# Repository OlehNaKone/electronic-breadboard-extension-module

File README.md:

# electronic-breadboard-extension-module

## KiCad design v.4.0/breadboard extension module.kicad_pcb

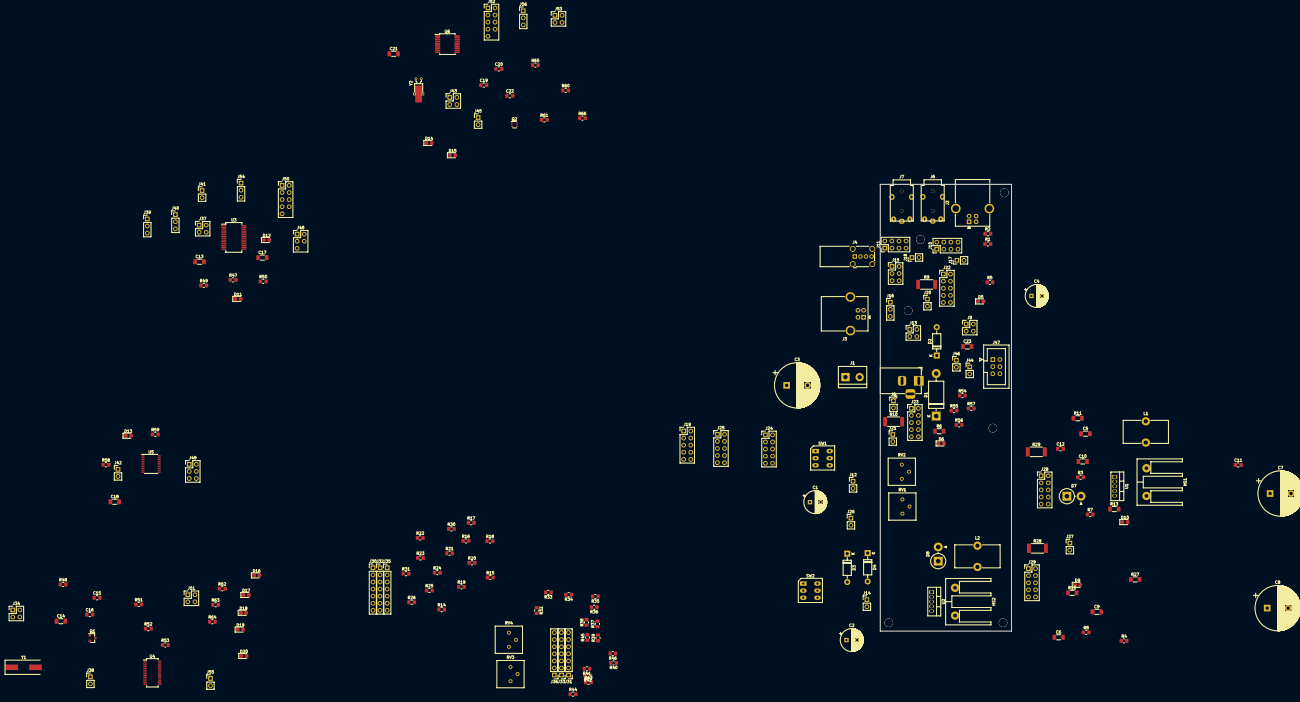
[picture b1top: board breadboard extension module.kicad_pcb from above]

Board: 2 copper layers, 47.0 x 160.0 mm, 185 parts (0 on the bottom side), 169 nets, no tracks yet.

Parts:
C1, C2: 100uF35V; CP_Radial_D8.0mm_P3.80mm
C3, C7, C8: 1000uF50V; CP_Radial_D16.0mm_P7.50mm
C4: 100uF16V; CP_Radial_D8.0mm_P3.80mm
C5, C6, C9, C10, C13: 100nF; C_1206_3216Metric_Pad1.33x1.80mm_HandSolder
C11, C12: 100nF; C_0805_2012Metric_Pad1.18x1.45mm_HandSolder
C14, C17, C18, C21, C23: 1uF; C_1206_3216Metric_Pad1.33x1.80mm_HandSolder
C15, C16: 1uF; C_0805_2012Metric_Pad1.18x1.45mm_HandSolder
C19, C20: 18pF; C_0805_2012Metric_Pad1.18x1.45mm_HandSolder
C22: 10nF; C_0805_2012Metric_Pad1.18x1.45mm_HandSolder
D1: 1N5408; D_DO-201AD_P15.24mm_Horizontal
D2, D3, D4: 1N5819; D_DO-41_SOD81_P10.16mm_Horizontal
D5: usbpower.red; LED_0805_2012Metric_Castellated
D6: mainpower.green; LED_0805_2012Metric_Castellated
D7, D8: 1N5822; D_DO-201AD_P5.08mm_Vertical_AnodeUp
D9: vinvreg.red; LED_0805_2012Metric_Castellated
D10: stdnreg.green; LED_0805_2012Metric_Castellated
D11: ft232.txd; LED_0805_2012Metric_Castellated
D12: ft232.rxd; LED_0805_2012Metric_Castellated
D13: avrisp.prog; LED_0805_2012Metric_Castellated
D14: ch340.txd; LED_0805_2012Metric_Castellated
D15: ch340.rxd; LED_0805_2012Metric_Castellated
D16: fe11s.port1; LED_0805_2012Metric_Castellated
D17: fe11s.port3; LED_0805_2012Metric_Castellated
D18: fe11s.port2; LED_0805_2012Metric_Castellated
D19: fe11s.port4; LED_0805_2012Metric_Castellated
D20: fe11s.active; LED_0805_2012Metric_Castellated
HS1: vinvreg.heatsink; Heatsink_16.36x16mm_2xFixation1.35mm
HS2: stdnreg.heatsink; Heatsink_16.36x16mm_2xFixation1.35mm
J1: Screw_Terminal_01x02; TerminalBlock_bornier-2_P5.08mm
J2: USB-B-1; USB_B_OST_USB-B1HSxx_Horizontal
J3: USB-B-2; USB_B_OST_USB-B1HSxx_Horizontal
J4: USB-A-1; USB_A_Wuerth_614004134726_Horizontal
J5: Barrel_Jack_Switch; BarrelJack_Horizontal
J6: AudioJack1; Jack_3.5mm_ST-17D-070_Horizontal
J7: AudioJack2; Jack_3.5mm_ST-17D-070_Horizontal
J8: mainpower.jackswitch; PinHeader_1x02_P2.54mm_Vertical
J9: usbpower.muxsw; PinHeader_2x02_P2.54mm_Vertical
J10: AudioJack1.conn; PinHeader_2x04_P2.54mm_Vertical
J11: AudioJack2.conn; PinHeader_2x04_P2.54mm_Vertical
J12: stdnreg.disable; PinHeader_1x02_P2.54mm_Vertical
J13: addusb.datasw; PinHeader_2x02_P2.54mm_Vertical
J14: vinvreg.disable; PinHeader_1x02_P2.54mm_Vertical
J15: addusb.vccsw; PinHeader_2x03_P2.54mm_Vertical
J16: usbb1.vccsw; PinHeader_1x03_P2.54mm_Vertical
J17: AudioJack1.gnd; PinHeader_1x02_P2.54mm_Vertical
J18: AudioJack2.gnd; PinHeader_1x02_P2.54mm_Vertical
J19, J24, J25: mainpower.gnd; PinHeader_2x05_P2.54mm_Vertical
J20: usbpower.current; PinHeader_1x02_P2.54mm_Vertical
J21: mainpower.current; PinHeader_1x02_P2.54mm_Vertical
J22: usbpower.vcc; PinHeader_2x05_P2.54mm_Vertical
J23: mainpower.vcc; PinHeader_2x05_P2.54mm_Vertical
J26: stdnreg.outcurrent; PinHeader_1x02_P2.54mm_Vertical
J27: vinvreg.outcurrent; PinHeader_1x02_P2.54mm_Vertical
J28: stdnreg.vout; PinHeader_2x05_P2.54mm_Vertical
J29: vinvreg.vout; PinHeader_2x05_P2.54mm_Vertical
J30, J32, J35: stdnreg.vsw; PinHeader_1x07_P2.54mm_Vertical
J31, J33, J36: vinveg.vsw; PinHeader_1x07_P2.54mm_Vertical
J34: fe11s.usbsw; PinHeader_2x02_P2.54mm_Vertical
J37: ft232.usbsw; PinHeader_2x02_P2.54mm_Vertical
J38: fe11s.vccsw; PinHeader_1x02_P2.54mm_Vertical
J39: ft232.ressw; PinHeader_1x03_P2.54mm_Vertical
J40: ft232.vcciosw; PinHeader_1x03_P2.54mm_Vertical
J41: ft232.vccsw; PinHeader_1x02_P2.54mm_Vertical
J42: buff.vccsw; PinHeader_1x02_P2.54mm_Vertical
J43: ch340.usbsw; PinHeader_2x02_P2.54mm_Vertical
J44: avrisp.ressw; PinHeader_1x02_P2.54mm_Vertical
J45: ch340.vccsw; PinHeader_1x02_P2.54mm_Vertical
J46: avrisp.vccsw; PinHeader_1x02_P2.54mm_Vertical
J47: AVR-ISP-6; IDC-Header_2x03_P2.54mm_Vertical
J48: ft232.addport; PinHeader_2Rows-05Pins_P2.54mm_Vertical
J49: buff.addport; PinHeader_2x03_P2.54mm_Vertical
J50: ft232.rs232port; PinHeader_2Rows-09Pins_P2.54mm_Vertical
J51: fe11s.addport; PinHeader_2x02_P2.54mm_Vertical
J52: ch340.rs232port; PinHeader_2Rows-09Pins_P2.54mm_Vertical
J53: ch340.addport; PinHeader_2x02_P2.54mm_Vertical
J54: ft232.uartport; PinHeader_1x03_P2.54mm_Vertical
J55: fe11s.connected; PinHeader_1x02_P2.54mm_Vertical
J56: ch340.uartport; PinHeader_1x03_P2.54mm_Vertical
L1: 300uH; L_Toroid_Vertical_L16.0mm_W8.0mm_P7.62mm
L2: 150 (68-220) uH; L_Toroid_Vertical_L16.0mm_W8.0mm_P7.62mm
Q1: BC847; SOT-23
Q2: BC857BDW1; SOT-363_SC-70-6
R1, R2: 10; R_0805_2012Metric_Pad1.20x1.40mm_HandSolder
R3, R4, R7, R8: 47k; R_0805_2012Metric_Pad1.20x1.40mm_HandSolder
R5, R51, R62, R63, R64: 2k; R_0805_2012Metric_Pad1.20x1.40mm_HandSolder
R6, R12, R13: 2.4k; R_1206_3216Metric_Pad1.30x1.75mm_HandSolder
R9, R10, R28, R29: 0.1R; R_2512_6332Metric_Pad1.40x3.35mm_HandSolder
R11, R27: 1.6k; R_1206_3216Metric_Pad1.30x1.75mm_HandSolder
R14, R32: 6.2k; R_0805_2012Metric_Pad1.20x1.40mm_HandSolder
R15, R33: 240 1%; R_0805_2012Metric_Pad1.20x1.40mm_HandSolder
R16, R34: 5.1k; R_0805_2012Metric_Pad1.20x1.40mm_HandSolder
R17, R25, R35, R43, R54, R55, R56, R57: 100; R_0805_2012Metric_Pad1.20x1.40mm_HandSolder
R18, R36: 3.3k 1%; R_0805_2012Metric_Pad1.20x1.40mm_HandSolder
R19, R37: 470 1%; R_0805_2012Metric_Pad1.20x1.40mm_HandSolder
R20, R38: 4.02k 1%; R_0805_2012Metric_Pad1.20x1.40mm_HandSolder
R21, R22, R39, R40: 20k 1%; R_0805_2012Metric_Pad1.20x1.40mm_HandSolder
R23, R41: 2.37k; R_0805_2012Metric_Pad1.20x1.40mm_HandSolder
R24, R42: 1.87k; R_0805_2012Metric_Pad1.20x1.40mm_HandSolder
R26, R44: 754.472; R_0805_2012Metric_Pad1.20x1.40mm_HandSolder
R30, R45: 2.37k 1%; R_0805_2012Metric_Pad1.20x1.40mm_HandSolder
R31, R46: 3.74k 1%; R_0805_2012Metric_Pad1.20x1.40mm_HandSolder
R47, R52, R53, R58, R61, R66: 10k; R_0805_2012Metric_Pad1.20x1.40mm_HandSolder
R48: 2k7 1%; R_0805_2012Metric_Pad1.20x1.40mm_HandSolder
R49, R50, R59, R60, R65: 1k; R_0805_2012Metric_Pad1.20x1.40mm_HandSolder
RV1, RV3: 45k; Potentiometer_Bourns_3386P_Vertical
RV2, RV4: 5k; Potentiometer_Bourns_3386P_Vertical
SW1, SW2: SW_Push_DPDT; SW_Push_DPDT_8.4x8.4mm
U1, U2: LM2596T-ADJ; TO-220-5_Vertical
U3: FT232RL; SSOP-28_5.3x10.2mm_P0.65mm
U4: FE1.1S; SSOP-28_3.9x9.9mm_P0.635mm
U5: 74HC244; SSOP-20_4.4x6.5mm_P0.65mm
U6: CH340T; SSOP-20_5.3x7.2mm_P0.65mm
Y1: 12MHz; Crystal_SMD_HC49-SD
Y2: 12MHz; Crystal_DS26_D2.0mm_L6.0mm_Horizontal_1EP_style2

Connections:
/AudioJack1.R1: J6.R1, J10.5, J10.6
/AudioJack1.R2: J6.R2, J10.3, J10.4
/AudioJack1.S: J6.S, J10.1, J10.2
/AudioJack1.T: J6.T, J10.7, J10.8
/AudioJack2.R1: J7.R1, J11.5, J11.6
/AudioJack2.R2: J7.R2, J11.3, J11.4
/AudioJack2.S: J7.S, J11.1, J11.2
/AudioJack2.T: J7.T, J11.7, J11.8
/avrisp.miso: R54.1, U5.2
/avrisp.mosi: R55.1, U5.16
/avrisp.progled: D13.1, U5.9
/avrisp.sck: R56.1, U5.14
/avrisp.~reset~: R57.1, U5.12
/buff.i0: J49.1, U5.17
/buff.i1: J49.3, U5.15
/buff.i2: J49.5, U5.13
/buff.o0: J49.2, U5.3
/buff.o1: J49.4, U5.5
/buff.o2: J49.6, U5.7
/ch340.ckoh: J53.1, U6.1
/ch340.ckol: J53.3, U6.2
/ch340.d+: J43.1, U4.11
/ch340.d-: J43.3, U4.10
/ch340.r232: J53.4, U6.18
/ch340.rxd: J52.2, J56.2, R66.2, U6.4
/ch340.txd: J52.3, J56.1, R61.2, U6.3
/ch340.~cts~: J52.8, U6.11
/ch340.~dcd~: J52.1, U6.14
/ch340.~dsr~: J52.6, U6.12
/ch340.~dtr~: J52.4, U6.15
/ch340.~nos~: J53.2, U6.20
/ch340.~ri~: J52.9, U6.13
/ch340.~rts~: J52.7, U6.16
/fe11s.connected: J39.1, J55.1, J55.2, Q1.3, R51.1
/fe11s.d+: J34.2, U4.16
/fe11s.d-: J34.4, U4.15
/fe11s.led13: R62.1, U4.23
/fe11s.led24: R63.1, U4.24
/fe11s.leddrv: D16.2, D17.1, D18.2, D19.1, D20.2, U4.22
/fe11s.p3d+: J51.1, U4.7
/fe11s.p3d-: J51.3, U4.6
/fe11s.p4d+: J51.2, U4.4
/fe11s.p4d-: J51.4, U4.5
/fe11s.vbus: C14.1, J38.2, R51.2, R52.1, R53.1, U4.18, U4.20
/fe11s.~connected~: Q1.1, R53.2, U4.25
/ft232.cbus0: D11.1, J48.1, U3.23
/ft232.cbus1: D12.1, J48.2, U3.22
/ft232.cbus2: J48.3, U3.13
/ft232.cbus3: J48.4, U3.14
/ft232.cbus4: J48.5, U3.12
/ft232.d+: J37.1, U4.9
/ft232.d-: J37.3, U4.8
/ft232.rxd: J50.2, J54.2, U3.5
/ft232.txd: J50.3, J54.1, U3.1
/ft232.~cts~: J50.8, R58.2, U3.11, U5.1, U5.11
/ft232.~dcd~: J50.1, U3.10, U5.4
/ft232.~dsr~: J50.6, U3.9, U5.8
/ft232.~dtr~: J50.4, U3.2, U5.18
/ft232.~ri~: J50.9, U3.6
/ft232.~rts~: J50.7, U3.3, U5.6
/mainpower.vcc: C3.1, D1.1, D2.1, J21.1, R6.2, R10.1, SW1.3, SW1.6, SW2.3, SW2.6
/stdnreg.1.81V: J30.1, R25.1, R26.2
/stdnreg.3.33V: J30.2, R23.1, R24.2
/stdnreg.5.15V: J30.3, R22.1, R23.2, R31.1
/stdnreg.7.5V: J30.4, R21.1, R22.2, R30.1, R31.2
/stdnreg.9.2V: J30.5, R20.1, R21.2, R30.2
/stdnreg.12.3V: J30.6, R19.1, R20.2
/stdnreg.15.2V: J30.7, R17.1, R18.2
/stdnreg.19.2V: J35.7, R15.1, R16.2
/stdnreg.24.15V: J35.6, R14.2
/stdnreg.coarse1: J35.2, RV1.1
/stdnreg.coarse2: J35.3, RV1.2, RV1.3
/stdnreg.fb: C12.1, J32.1, J32.2, J32.3, J32.4, J32.5, J32.6, J32.7, R11.1, U1.4
/stdnreg.fine1: J35.4, RV2.1
/stdnreg.fine2: J35.5, RV2.2, RV2.3
/stdnreg.vout: C12.2, J26.2, J28.1, J28.2, J28.3, J28.4, J28.5, J28.6, J28.7, J28.8, J28.9, J28.10, J35.1, R26.1, R29.2
/usba1.d+: J4.3, J13.2
/usba1.d-: J4.2, J13.4
/usba1.vbus: J4.1, J15.4, J15.6
/usbb1.d+: J34.1, R1.2
/usbb1.d-: J34.3, R2.2
/usbb1.vbus: J2.1, J16.1, J16.2
/usbb2.d+: J3.3, J13.1
/usbb2.d-: J3.2, J13.3
/usbb2.vbus: J3.1, J15.3, J15.5
/usbpower.vcc: C4.1, J9.1, J9.3, J15.1, J15.2, J16.3, J20.1, J38.1, J41.1, J42.1, J45.1, J46.1, R5.2, R9.1
/vinvreg.1.81V: J31.1, R43.1, R44.2
/vinvreg.3.33V: J31.2, R41.1, R42.2
/vinvreg.5.15V: J31.3, R40.1, R41.2, R46.1
/vinvreg.7.5V: J31.4, R39.1, R40.2, R45.1, R46.2
/vinvreg.9.2V: J31.5, R38.1, R39.2, R45.2
/vinvreg.12.3V: J31.6, R37.1, R38.2
/vinvreg.15.2V: J31.7, R35.1, R36.2
/vinvreg.19.2V: J36.7, R33.1, R34.2
/vinvreg.24.15V: J36.6, R32.2
/vinvreg.coarse1: J36.2, RV3.1
/vinvreg.coarse2: J36.3, RV3.2, RV3.3
/vinvreg.fb: C11.1, J33.1, J33.2, J33.3, J33.4, J33.5, J33.6, J33.7, R27.2, U2.4
/vinvreg.fine1: J36.4, RV4.1
/vinvreg.fine2: J36.5, RV4.2, RV4.3
/vinvreg.vout: J27.2, J29.1, J29.2, J29.3, J29.4, J29.5, J29.6, J29.7, J29.8, J29.9, J29.10, R27.1, R28.2
GNDD: C1.2, C2.2, C3.2, C4.2, C7.2, C8.1, C9.1, C10.2, C11.2, C13.1, C14.2, C15.1, C16.1, C17.2, C18.2, C19.1, C20.1, C21.1, C22.1, C23.2, D4.2, D5.1, D6.1, D7.2, D10.1, D14.1, D15.1, J1.2, J2.4, J2.5, J3.4, J3.5, J4.4, J4.5, J5.2, J17.1, J17.2, J18.1, J18.2, J19.1, J19.2, J19.3, J19.4, J19.5, J19.6, J19.7, J19.8, J19.9, J19.10, J24.1, J24.2, J24.3, J24.4, J24.5, J24.6, J24.7, J24.8, J24.9, J24.10, J25.1, J25.2, J25.3, J25.4, J25.5, J25.6, J25.7, J25.8, J25.9, J25.10, J36.1, J47.6, J50.5, J52.5, J54.3, J56.3, L2.2, Q1.2, R7.2, R11.2, R12.1, R44.1, R47.1, R48.1, R64.1, U1.3, U3.7, U3.18, U3.21, U3.25, U3.26, U4.1, U4.19, U5.10, U5.19, U6.8
unnamed: C1.1, C5.1, J12.1, SW1.2, SW1.5, U1.1
unnamed: C2.1, D3.2, SW2.2, SW2.5
unnamed: C5.2, J12.2, R3.2
unnamed: C6.1, D3.1, D4.1, U2.1
unnamed: C6.2, R4.2
unnamed: C8.2, C9.2, D8.2, D9.1, J14.2, J27.1, R8.2, R28.1, U2.3
unnamed: C7.1, C10.1, J26.1, L1.2, R13.2, R29.1
unnamed: C13.2, J40.1, U3.17
unnamed: C15.2, U4.13, U4.21
unnamed: C16.2, U4.28
unnamed: C17.1, J39.3, J40.3, J41.2, R49.1, R50.1, U3.20
unnamed: C18.1, J42.2, R58.1, R59.1, U5.20
unnamed: C19.2, U6.9, Y2.1
unnamed: C20.2, U6.10, Y2.2
unnamed: C21.2, J45.2, R60.1, R65.1, U6.19
unnamed: C22.2, U6.5
unnamed: C23.1, J46.2, J47.2
unnamed: D1.2, J1.1, J5.1
unnamed: D2.2, J9.2, J9.4
unnamed: D5.2, R5.1
unnamed: D6.2, R6.1
unnamed: D7.1, L1.1, U1.2
unnamed: D8.1, L2.1, U2.2
unnamed: D9.2, R12.2
unnamed: D10.2, R13.1
unnamed: D11.2, R49.2
unnamed: D12.2, R50.2
unnamed: D13.2, R59.2
unnamed: D14.2, Q2.3
unnamed: D15.2, Q2.6
unnamed: D16.1, D17.2, R62.2
unnamed: D18.1, D19.2, R63.2
unnamed: D20.1, R64.2
unnamed: J2.2, R2.1
unnamed: J2.3, R1.1
unnamed: J5.3, J8.1, J8.2
unnamed: J14.1, R4.1, R8.1, U2.5
unnamed: J20.2, J22.1, J22.2, J22.3, J22.4, J22.5, J22.6, J22.7, J22.8, J22.9, J22.10, R9.2
unnamed: J21.2, J23.1, J23.2, J23.3, J23.4, J23.5, J23.6, J23.7, J23.8, J23.9, J23.10, R10.2
unnamed: J37.2, U3.15
unnamed: J37.4, U3.16
unnamed: J39.2, R47.2, U3.19
unnamed: J40.2, U3.4
unnamed: J43.2, U6.6
unnamed: J43.4, U6.7
unnamed: J44.1, R57.2
unnamed: J44.2, J47.5
unnamed: J47.1, R54.2
unnamed: J47.3, R56.2
unnamed: J47.4, R55.2
unnamed: Q2.1, R65.2
unnamed: Q2.2, R66.1
unnamed: Q2.4, R60.2
unnamed: Q2.5, R61.1
unnamed: R3.1, R7.1, U1.5
unnamed: R14.1, R15.2
unnamed: R16.1, R17.2
unnamed: R18.1, R19.2
unnamed: R24.1, R25.2
unnamed: R32.1, R33.2
unnamed: R34.1, R35.2
unnamed: R36.1, R37.2
unnamed: R42.1, R43.2
unnamed: R48.2, U4.14
unnamed: R52.2, U4.26
unnamed: U4.2, Y1.1
unnamed: U4.3, Y1.2

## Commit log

2022-04-06 init
